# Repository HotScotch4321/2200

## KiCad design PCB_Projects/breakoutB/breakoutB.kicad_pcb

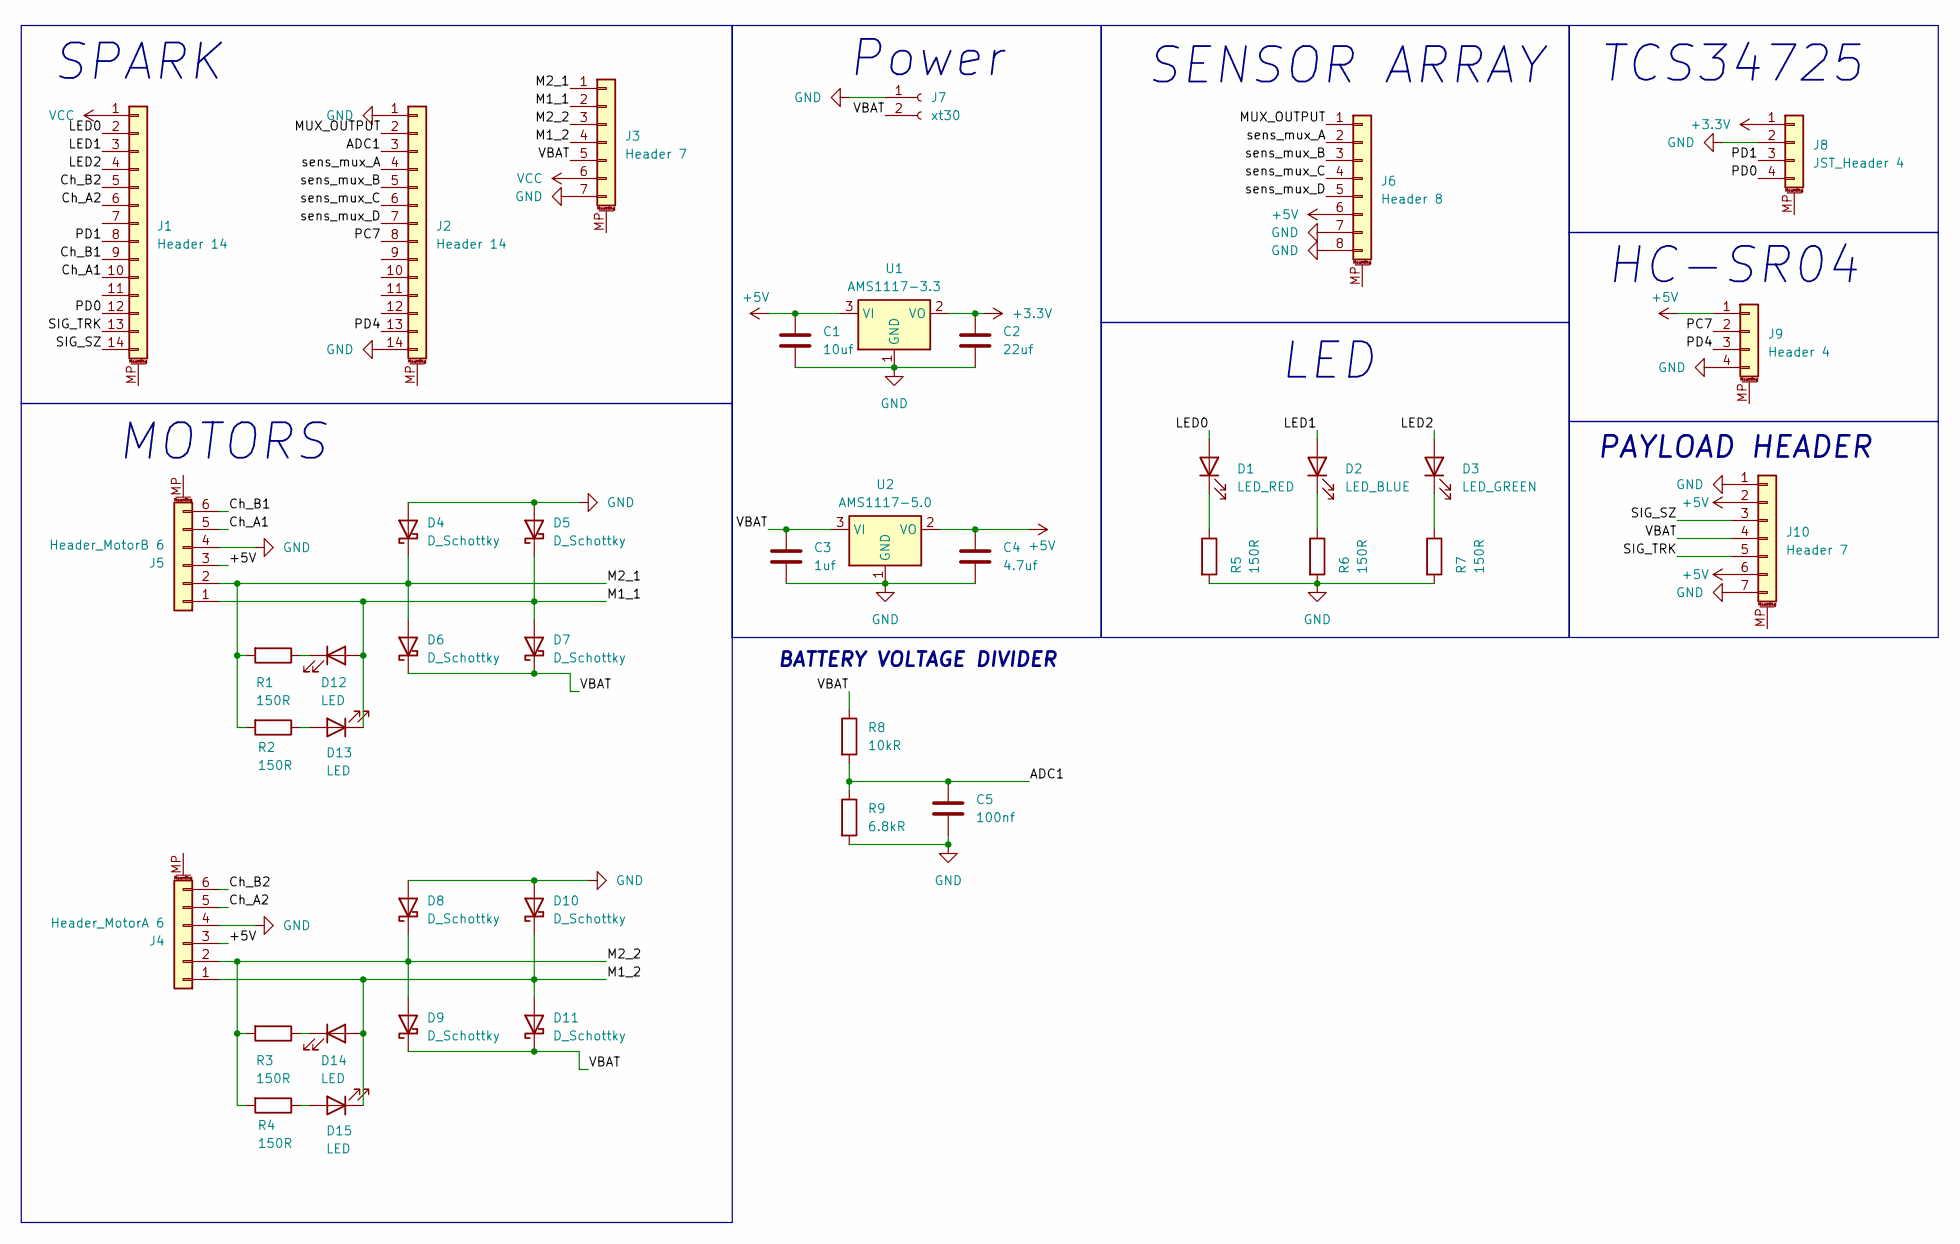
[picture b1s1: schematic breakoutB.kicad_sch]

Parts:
C1: 10uf; C_1206_3216Metric
C2: 22uf; C_1206_3216Metric
C3: 1uf; C_1206_3216Metric
C4: 4.7uf; C_1206_3216Metric
C5: 100nf; C_1206_3216Metric
D1: LED_RED; LED_D5.0mm
D2: LED_BLUE; LED_D5.0mm
D3: LED_GREEN; LED_D5.0mm
D4, D5, D6, D7, D8, D9, D10, D11: D_Schottky; D_SMB
D12, D13, D14, D15: LED; LED_0603_1608Metric
J1, J2: Header 14; PinSocket_1x14_P2.54mm_Vertical
J3: Header 7; PinSocket_1x07_P2.54mm_Vertical
J4: Header_MotorA 6; JST_EH_S6B-EH_1x06_P2.50mm_Horizontal
J5: Header_MotorB 6; JST_EH_S6B-EH_1x06_P2.50mm_Horizontal
J6: Header 8; PinSocket_1x08_P2.54mm_Vertical
J7: xt30; AMASS_XT30PW-M_1x02_P2.50mm_Horizontal
J8: JST_Header 4; JST_PH_S4B-PH-K_1x04_P2.00mm_Horizontal
J9: Header 4; PinSocket_1x04_P2.54mm_Vertical
J10: Header 7; JST_EH_B7B-EH-A_1x07_P2.50mm_Vertical
R1, R2, R3, R4, R5, R6, R7: 150R; R_0603_1608Metric
R8: 10kR; R_0603_1608Metric
R9: 6.8kR; R_0603_1608Metric
U1: AMS1117-3.3; SOT-223-3_TabPin2
U2: AMS1117-5.0; SOT-223-3_TabPin2

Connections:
+3.3V: C2.1, J8.1, U1.2 (VO)
+5V: C1.1, C4.1, J4.3, J5.3, J6.6, J9.1, J10.2, J10.6, U1.3 (VI), U2.2 (VO)
/ADC1: C5.1, J2.3, R8.2, R9.1
/Ch_A1: J1.10, J5.5
/Ch_A2: J1.6, J4.5
/Ch_B1: J1.9, J5.6
/Ch_B2: J1.5, J4.6
/LED0: D1.2 (A), J1.2
/LED1: D2.2 (A), J1.3
/LED2: D3.2 (A), J1.4
/M1_1: D5.1 (K), D7.2 (A), D12.2 (A), D13.1 (K), J3.2, J5.1
/M1_2: D10.1 (K), D11.2 (A), D14.2 (A), D15.1 (K), J3.4, J4.1
/M2_1: D4.1 (K), D6.2 (A), J3.1, J5.2, R1.2, R2.2
/M2_2: D8.1 (K), D9.2 (A), J3.3, J4.2, R3.2, R4.2
/MUX_OUTPUT: J2.2, J6.1
/PC7: J2.8, J9.2
/PD0: J1.12, J8.4
/PD1: J1.8, J8.3
/PD4: J2.13, J9.3
/SIG_SZ: J1.14, J10.3
/SIG_TRK: J1.13, J10.5
/VBAT: C3.1, D6.1 (K), D7.1 (K), D9.1 (K), D11.1 (K), J3.5, J7.2, J10.4, R8.1, U2.3 (VI)
/sens_mux_A: J2.4, J6.2
/sens_mux_B: J2.5, J6.3
/sens_mux_C: J2.6, J6.4
/sens_mux_D: J2.7, J6.5
GND: C1.2, C2.2, C3.2, C4.2, C5.2, D4.2 (A), D5.2 (A), D8.2 (A), D10.2 (A), J2.1, J2.14, J3.7, J4.4, J5.4, J6.7, J6.8, J7.1, J8.2, J9.4, J10.1, J10.7, R5.2, R6.2, R7.2, R9.2, U1.1 (GND), U2.1 (GND)
unnamed: D1.1 (K), R5.1
unnamed: D2.1 (K), R6.1
unnamed: D3.1 (K), R7.1
unnamed: D12.1 (K), R1.1
unnamed: D13.2 (A), R2.1
unnamed: D14.1 (K), R3.1
unnamed: D15.2 (A), R4.1
PB7: J1.11
VCC: J1.1, J3.6
adc11: J2.10

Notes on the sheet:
PAYLOAD HEADER
MOTORS
HC-SR04
SENSOR ARRAY
Power
BATTERY VOLTAGE DIVIDER
TCS34725
LED
SPARK

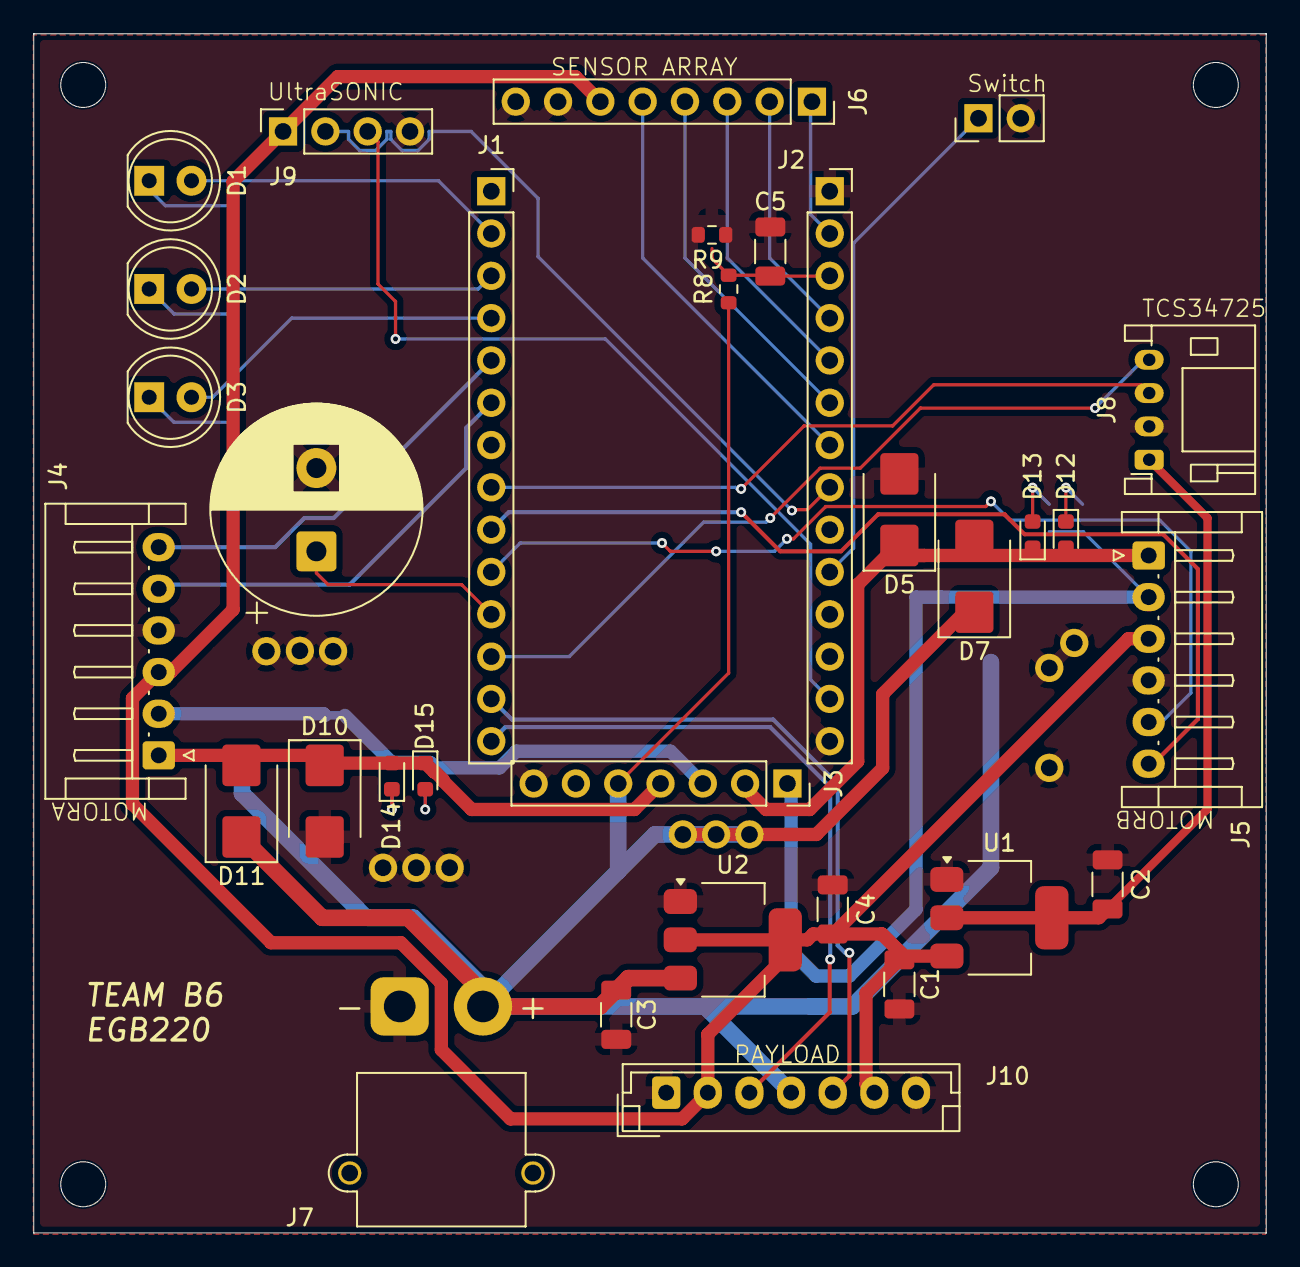
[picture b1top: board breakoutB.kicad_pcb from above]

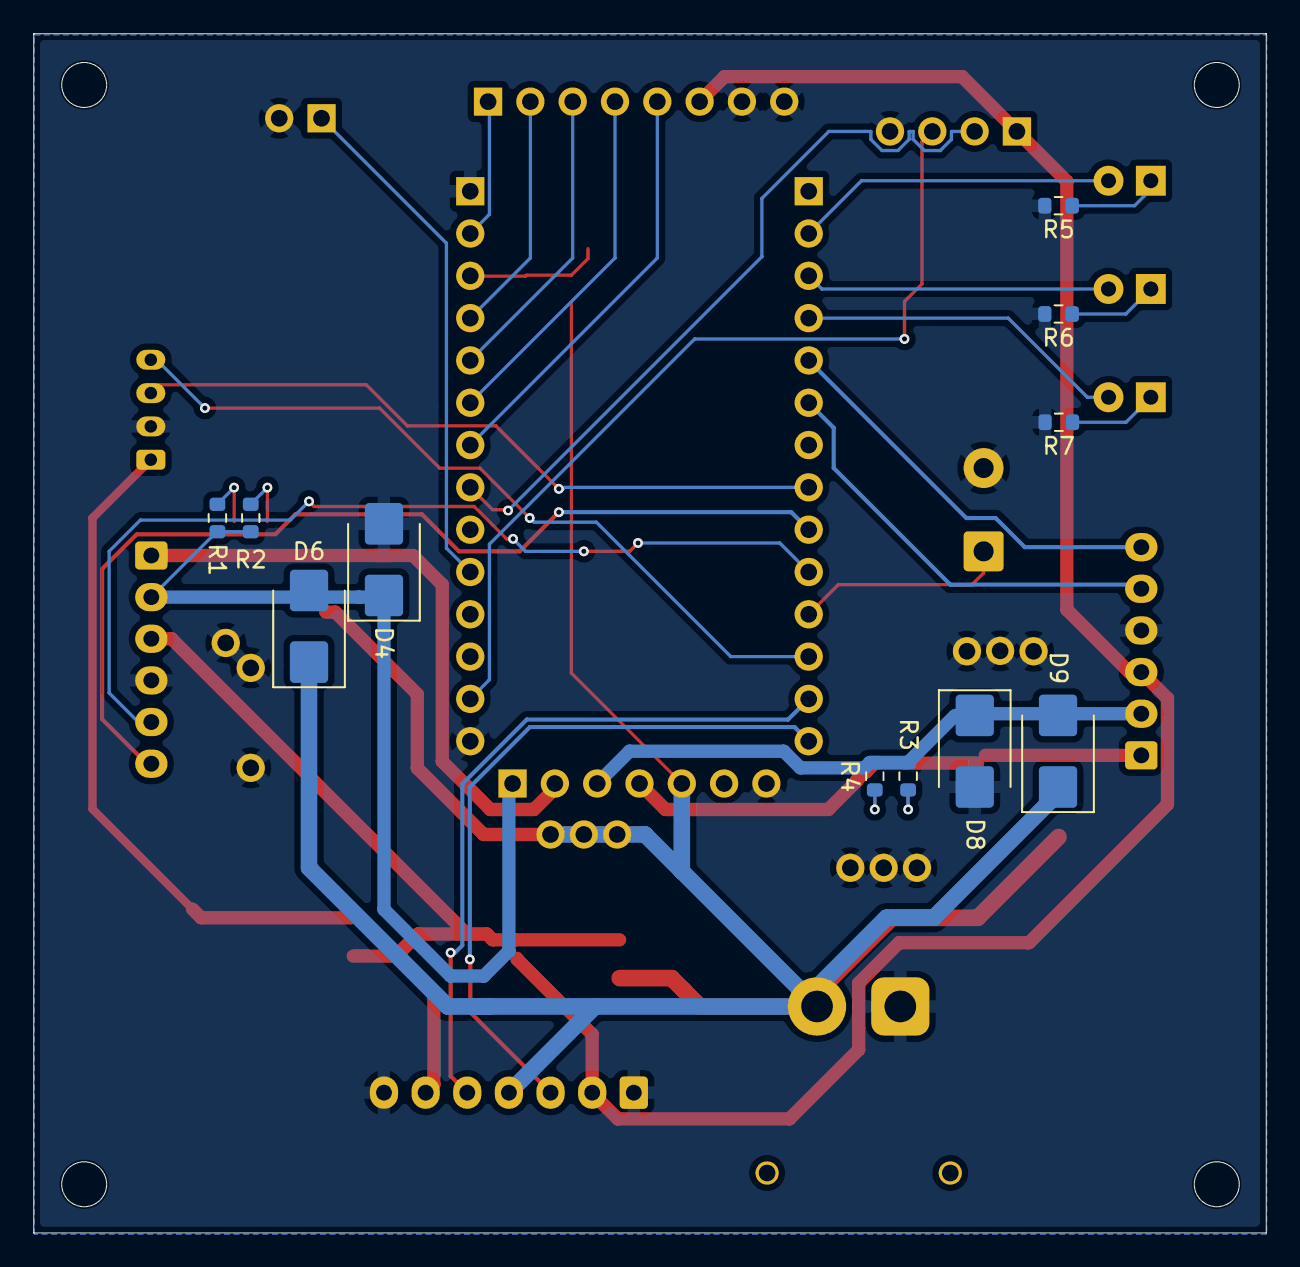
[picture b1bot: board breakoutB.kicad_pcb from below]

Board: 2 copper layers, 74.0 x 72.0 mm, 41 parts (11 on the bottom side), 35 nets.

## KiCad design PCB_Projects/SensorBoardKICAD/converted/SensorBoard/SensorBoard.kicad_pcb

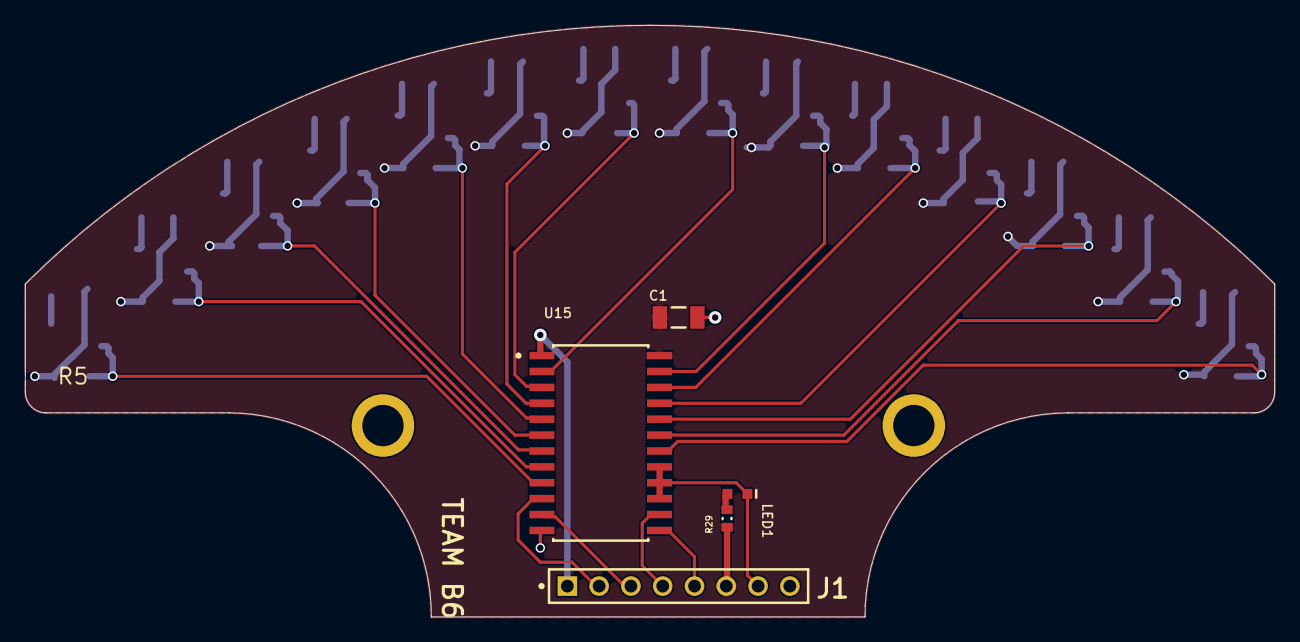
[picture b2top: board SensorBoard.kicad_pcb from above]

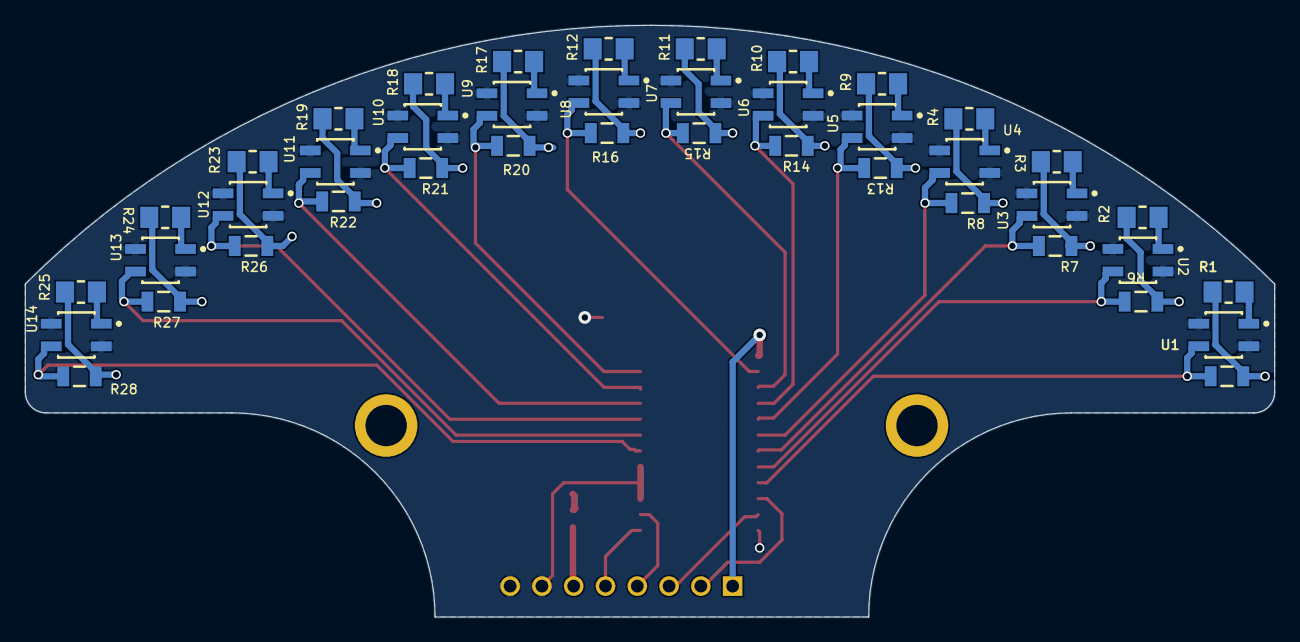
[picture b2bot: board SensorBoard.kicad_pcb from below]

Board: 2 copper layers, 99.8 x 47.3 mm, 47 parts (42 on the bottom side), 36 nets.

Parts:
C1: CAP 100nF 100V 1206(3216); CAPC1206(3216)150_N
J1: TSW-108-08-G-S; FP-TSW-108-08-G-S-MFG
LED1: 2V 20mA 0603 Red; 0603_A
R1, R2, R3, R4, R9, R10, R11, R12, R17, R18, R19, R23, R24, R25: RNCP1206FTD200R; FP-RNCP1206-IPC_B
R5, R6, R7, R8, R13, R14, R15, R16, R20, R21, R22, R26, R27, R28: CRGCQ1206J10K; FP-CRGCQ1206-IPC_C
R29: 150R 5% 0603(1608); RESC0603(1608)_L
U1, U2, U3, U4, U5, U6, U7, U8, U9, U10, U11, U12, U13, U14: QRE1113GR; FP-100CY-MFG
U15: CD74HC4067M96; FP-DW0024A-MFG

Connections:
+5: C1.1, J1.6, R1.2, R2.2, R3.2, R4.2, R5.1, R6.1, R7.1, R8.1, R9.2, R10.2, R11.2, R12.2, R13.1, R14.1, R15.1, R16.1, R17.2, R18.2, R19.2, R20.1, R21.1, R22.1, R23.2, R24.2, R25.2, R26.1, R27.1, R28.1, R29.2, U15.24
GND: C1.2, J1.7, J1.8, LED1.1, U1.2, U1.4, U2.2, U2.4, U3.2, U3.4, U4.2, U4.4, U5.2, U5.4, U6.2, U6.4, U7.2, U7.4, U8.2, U8.4, U9.2, U9.4, U10.2, U10.4, U11.2, U11.4, U12.2, U12.4, U13.2, U13.4, U14.2, U14.4, U15.12, U15.15, U15.16, U15.17
MUX_OUTPUT: J1.1, U15.1
NetLED1_2: LED1.2, R29.1
NetR1_1: R1.1, U1.1
NetR2_1: R2.1, U2.1
NetR3_1: R3.1, U3.1
NetR4_1: R4.1, U4.1
NetR9_1: R9.1, U5.1
NetR10_1: R10.1, U6.1
NetR11_1: R11.1, U7.1
NetR12_1: R12.1, U8.1
NetR17_1: R17.1, U9.1
NetR18_1: R18.1, U10.1
NetR19_1: R19.1, U11.1
NetR23_1: R23.1, U12.1
NetR24_1: R24.1, U13.1
NetR25_1: R25.1, U14.1
SENS_MUX_A: J1.2, U15.10
SENS_MUX_B: J1.3, U15.11
SENS_MUX_C: J1.4, U15.14
SENS_MUX_D: J1.5, U15.13
sense_1: R5.2, U1.3, U15.9
sense_2: R6.2, U2.3, U15.8
sense_3: R7.2, U3.3, U15.7
sense_4: R8.2, U4.3, U15.6
sense_5: R13.2, U5.3, U15.5
sense_6: R14.2, U6.3, U15.4
sense_7: R15.2, U7.3, U15.3
sense_8: R16.2, U8.3, U15.2
sense_9: R20.2, U9.3, U15.23
sense_10: R21.2, U10.3, U15.22
sense_11: R22.2, U11.3, U15.21
sense_12: R26.2, U12.3, U15.20
sense_13: R27.2, U13.3, U15.19
sense_14: R28.2, U14.3, U15.18

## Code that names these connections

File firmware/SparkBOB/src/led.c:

#include <avr/io.h>
#include "led.h"

// LED0: PE6 LED1: PB0 LED2: PB1 LED3: PB2 LED4: PB7 LED5: PD0 LED6: PB6 LED7: PB5 
void init_LEDS()
{
    // Set all LED pins as outputs
    DDRB |= (1 << PB0) | (1 << PB1) | (1 << PB2) | (1 << PB5) | (1 << PB6) | (1 << PB7);
    DDRD |= (1 << PD0);
    DDRE |= (1 << PE6);
}

void LED_on(uint8_t led_num)
{
    switch (led_num) {
        case 0: PORTE |= (1 << PORTE6); break;
        case 1: PORTB |= (1 << PORTB0); break;
        case 2: PORTB |= (1 << PORTB1); break;
        case 3: PORTB |= (1 << PORTB2); break;
        case 4: PORTB |= (1 << PORTB7); break;
        case 5: PORTD |= (1 << PORTD0); break;
        case 6: PORTB |= (1 << PORTB6); break;
        case 7: PORTB |= (1 << PORTB5); break;
    }
}

void LED_off(uint8_t led_num)
{
    switch (led_num) {
        case 0: PORTE &= ~(1 << PORTE6); break;
        case 1: PORTB &= ~(1 << PORTB0); break;
        case 2: PORTB &= ~(1 << PORTB1); break;
        case 3: PORTB &= ~(1 << PORTB2); break;
        case 4: PORTB &= ~(1 << PORTB7); break;
        case 5: PORTD &= ~(1 << PORTD0); break;
        case 6: PORTB &= ~(1 << PORTB6); break;
        case 7: PORTB &= ~(1 << PORTB5); break;
    }
}

// PC6 and PC7 are buttons, they are active low, so we can set them as input with pull-up resistors
void init_buttons()
{
    DDRC &= ~((1 << DDC6) | (1 << DDC7)); // set PC6 and PC7 as input
    PORTC |= (1 << PORTC6) | (1 << PORTC7); // enable pull-up resistors on PC6 and PC7
}

void button_led_control()
{
    if (!(PINC & (1 << PINC6))) { 
        LED_on(0); // turn on LED0 
    } else {
        PORTE &= ~(1 << PORTE6); 
    }

    if (!(PINC & (1 << PINC7))) { 
        LED_on(1); // turn on LED1 
    } else {
        PORTB &= ~(1 << PORTB0); 
    }
}

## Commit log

2026-03-09 Add initial firmware structure with LED, sensor, and timer functionalities
2026-03-09 Refactor LED and sensor functionalities: update LED_on function signature, implement LED_off function, and enhance sensor reading logic
2026-03-11 Add PCB project assets and update firmware main.c
    Import a large set of PCB project files (BOM, schematics, PCB docs, previews, STEP export, DRC/outputs, project structure) and numerous history/backup ZIPs under PCB_Projects. Also modify firmware/Sp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
2026-03-15 feat: Implement motor and LED control firmware and establish initial PCB project files.
2026-04-05 feat: update firmware source files and finalize PCB design project outputs
2026-04-05 feat: implement PID control logic and initialize KiCad project version history
2026-05-04 feat: PCB & tweak code
2026-05-27 Add initial firmware structure and implement core functionalities
    - Created header files for battery, encoder, LED, multiplexer, PID controller, TCS34725 color sensor, TWI communication, and ultrasonic sensor.
    - Implemented source files for battery management, encoder reading, LED control, multiplexer handling, PID control logic, TCS34725 sensor interaction, TWI communication, and ultrasonic distance measu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
    - Established a PlatformIO project configuration with a README for library management.
    - Developed a main application loop for robot control, including state management for line following and obstacle detection.
    - Added test files for unit testing and sensor verification.
2026-05-27 history
2026-05-27 refactor: clean up comments and improve ADC warm-up logic in mux and tcs34725 modules
2026-05-27 switch code
2026-05-28 added motors
2026-05-28 feat: add indicators functionality and refactor related components
2026-05-28 refactor: update finish marker detection logic and clean up sensor handling
2026-05-28 drive
2026-05-29 refactor: update LED handling and bump switch initialization
2026-05-29 feat: add motor PWM pause and resume functions
2026-05-30 testing
2026-05-30 images from python
